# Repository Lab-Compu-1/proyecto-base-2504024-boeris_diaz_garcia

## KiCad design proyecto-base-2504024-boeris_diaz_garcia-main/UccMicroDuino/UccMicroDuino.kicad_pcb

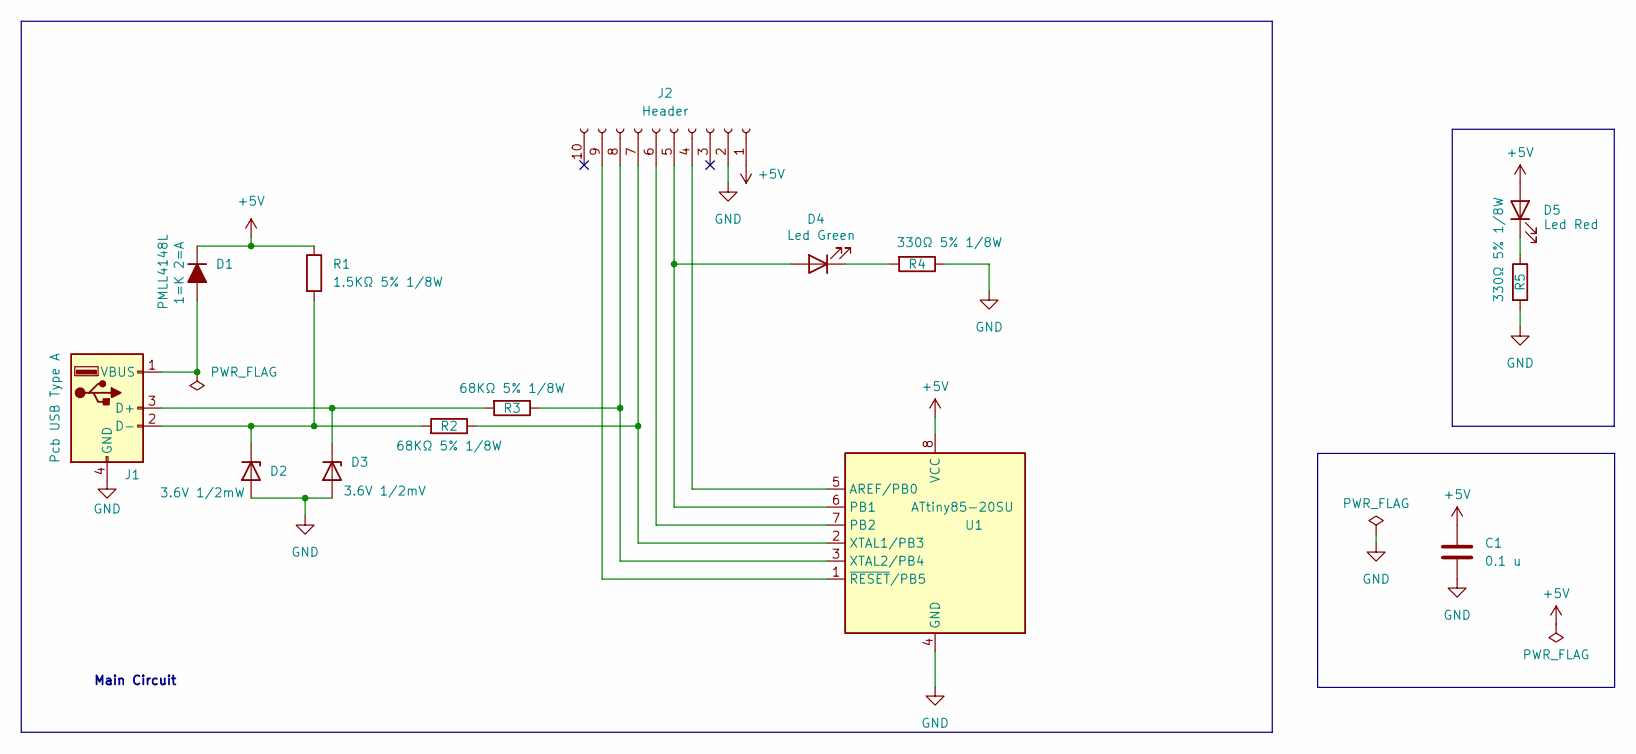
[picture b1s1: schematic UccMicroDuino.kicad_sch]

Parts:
C1: 0.1 u; C_0805_2012Metric_Pad1.18x1.45mm_HandSolder
D1: PMLL4148L; D_MELF_Handsoldering
D2: 3.6V 1/2mW; D_SOD-123
D3: 3.6V 1/2mV; D_SOD-123
D4: Led Green; ledSMD
D5: Led Red; ledSMD
J1: Pcb USB Type A; USB_A_UCC
J2: Header; PinSocket_1x10_P2.54mm_Vertical
R1: 1.5KΩ 5% 1/8W; R_0805_2012Metric_Pad1.20x1.40mm_HandSolder
R2, R3: 68KΩ 5% 1/8W; R_0805_2012Metric_Pad1.20x1.40mm_HandSolder
R4, R5: 330Ω 5% 1/8W; R_0805_2012Metric_Pad1.20x1.40mm_HandSolder
U1: ATtiny85-20SU; SOIC-8W_5.3x5.3mm_P1.27mm

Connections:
+5V: C1.1, D1.1 (K), D5.2 (A), J2.1, R1.1, U1.8 (VCC)
GND: C1.2, D2.2 (A), D3.2 (A), J1.4 (GND), J2.2, R4.1, R5.2, U1.4 (GND)
unnamed: D1.2 (A), J1.1 (VBUS)
unnamed: D2.1 (K), J1.2 (D-), R1.2, R2.2
unnamed: D3.1 (K), J1.3 (D+), R3.2
unnamed: D4.2 (A), J2.5, U1.6 (PB1)
unnamed: D4.1 (K), R4.2
unnamed: D5.1 (K), R5.1
unnamed: J2.4, U1.5 (AREF/PB0)
unnamed: J2.6, U1.7 (PB2)
unnamed: J2.7, R2.1, U1.2 (XTAL1/PB3)
unnamed: J2.8, R3.1, U1.3 (XTAL2/PB4)
unnamed: J2.9, U1.1 (~RESET/PB5)

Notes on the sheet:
Main Circuit

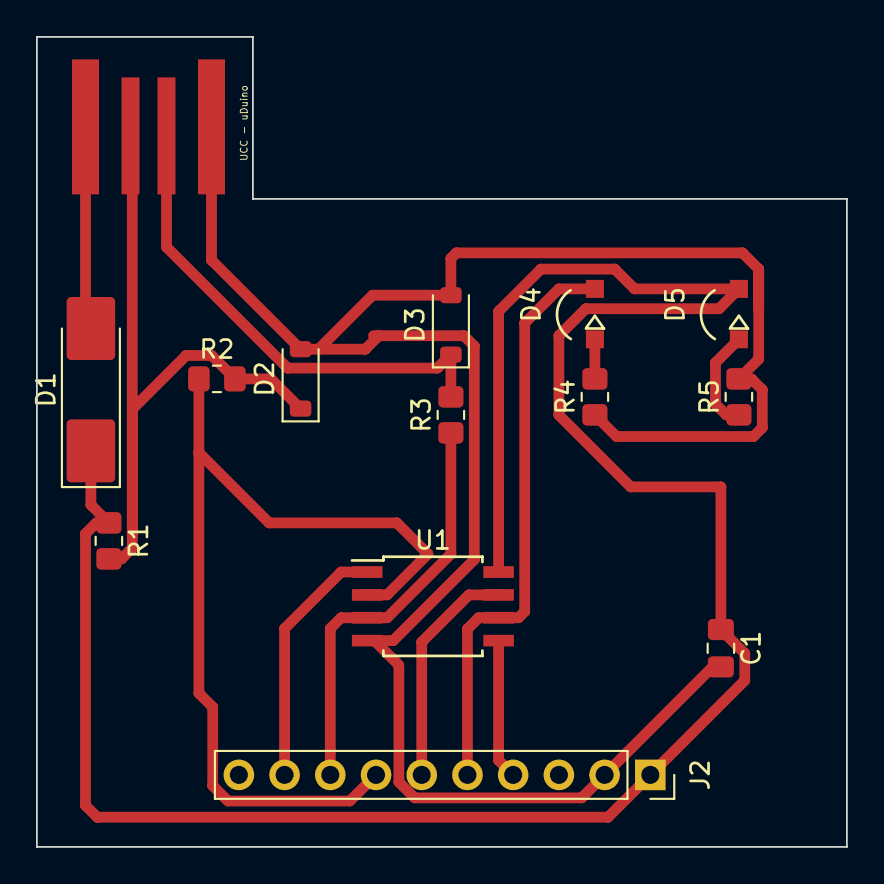
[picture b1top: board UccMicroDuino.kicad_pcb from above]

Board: 2 copper layers, 45.0 x 45.0 mm, 14 parts (0 on the bottom side), 13 nets.

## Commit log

2025-03-31 GitHub Classroom Feedback
2025-03-31 Setting up GitHub Classroom Feedback
